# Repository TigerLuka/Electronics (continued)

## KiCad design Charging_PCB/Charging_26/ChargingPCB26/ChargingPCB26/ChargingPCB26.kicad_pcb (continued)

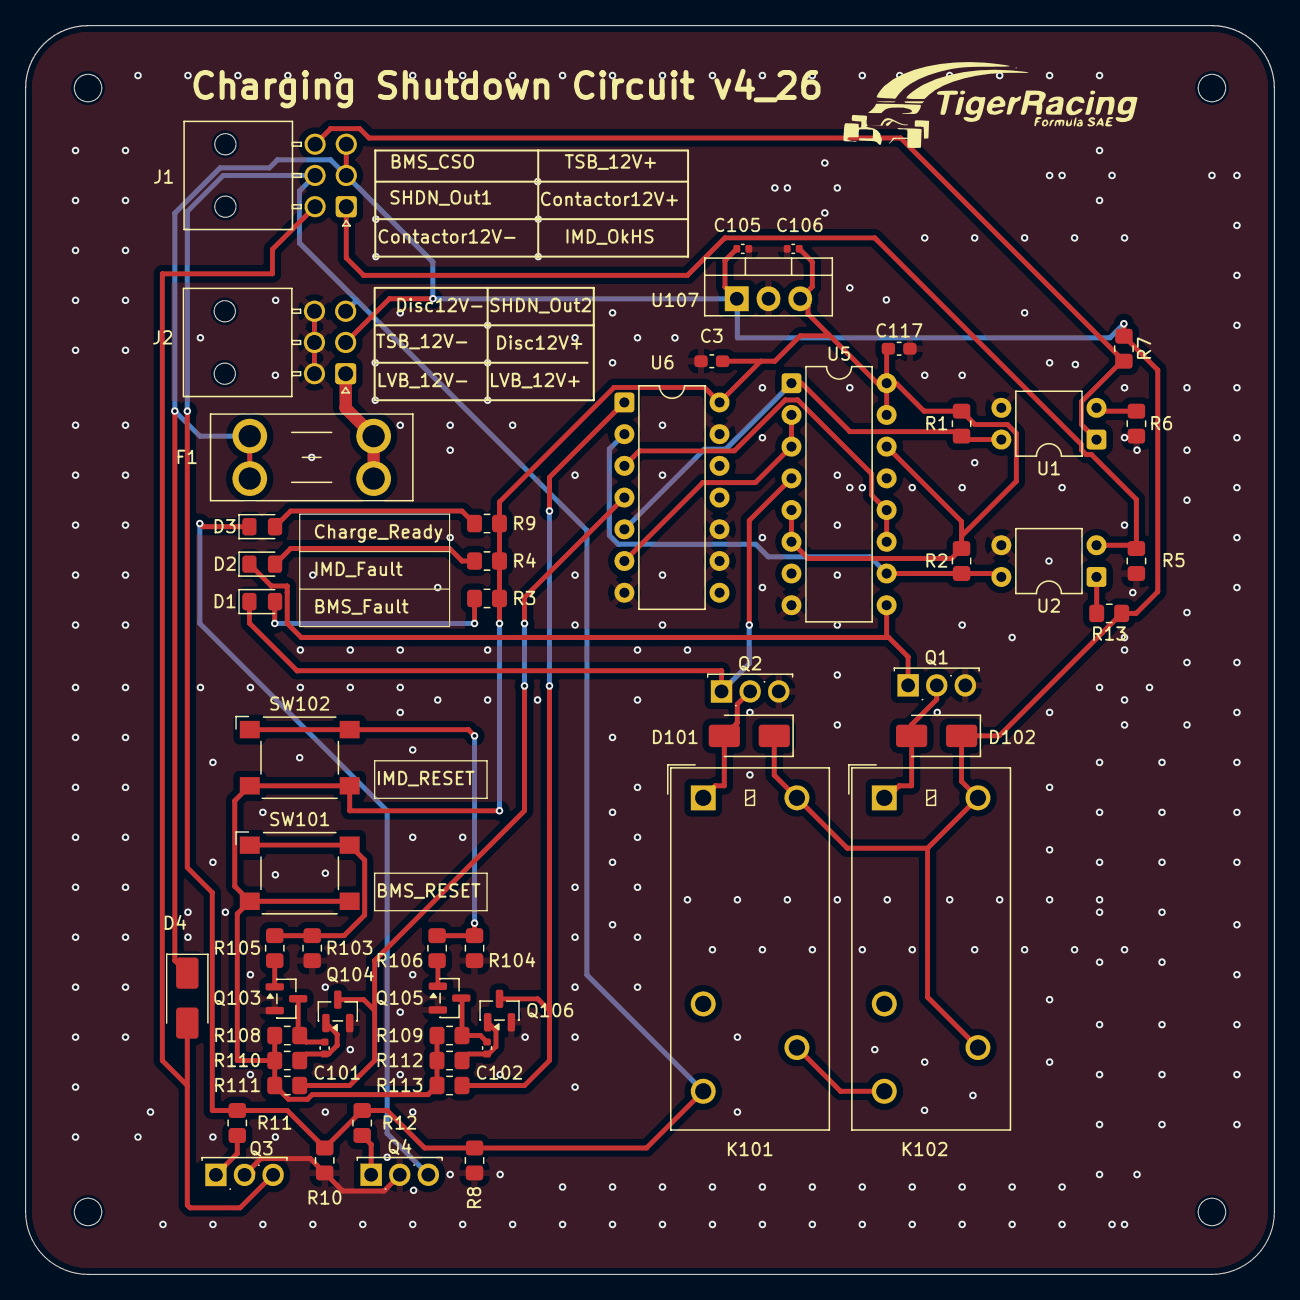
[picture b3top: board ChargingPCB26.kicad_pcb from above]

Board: 2 copper layers, 100.0 x 100.0 mm, 59 parts (0 on the bottom side), 35 nets.

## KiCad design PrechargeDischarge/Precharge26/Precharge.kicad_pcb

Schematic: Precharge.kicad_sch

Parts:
C1, C2, C11, C12, C15, C16, C17, C18, C19, C20, C21, C22, C23: 100n; C_0805_2012Metric_Pad1.15x1.40mm_HandSolder
C3, C8, C9, C10: 1u; C_0805_2012Metric_Pad1.15x1.40mm_HandSolder
C4, C5: 220u; C_Elec_6.3x5.4
C6, C7: 220u; C_Elec_6.3x5.4; not fitted
C13, C14: 10n; C_0805_2012Metric_Pad1.15x1.40mm_HandSolder
D1, D7, D8, D9, D12: D; D_SMA
D2, D3, D4, D5: LED; LED_0805_2012Metric_Castellated
D6: BZX84C3V3; D_SOT-23_ANK
D10, D11: BZX84C12; D_SOT-23_ANK
J1: MicroFit; Molex_Micro-Fit_3.0_43045-0812_2x04_P3.00mm_Vertical
J2: Mini-Fit_Jr_5566-04A; MICROFIT-4PIN
J3: 447690401; MICROFIT-4PIN
JP1, JP2, JP3: SolderJumper_2_Open; SolderJumper-2_P1.3mm_Open_RoundedPad1.0x1.5mm
K1: OMRON-G2RL-24; OMRON-G2R-24; JLC C1524522
K2: G7L-2A-X-L
Q1, Q3: 2N7002; SOT-23
Q2: MMBT3906; SOT-23
R1: 160; R_1206_3216Metric
R2, R3, R4, R5: 200; R_1206_3216Metric
R6, R9: 20k; R_1206_3216Metric
R7, R10, R23, R24: 6k8; R_1206_3216Metric
R8, R21, R27, R29, R44, R45, R48: 10k; R_1206_3216Metric
R11, R12: 1k5; R_1206_3216Metric
R13, R17, R26: 12k; R_1206_3216Metric
R14, R16: 47; R_1206_3216Metric
R15, R18: 560; R_1206_3216Metric
R19, R47: 220; R_1206_3216Metric
R20, R22, R25, R28: 100k; R_1206_3216Metric
R30: 500k; R_1206_3216Metric; not fitted
R31, R32, R33, R34, R36, R37, R38, R40, R41, R42: 510k; R_1206_3216Metric
R35: 2k2; R_1206_3216Metric
R39, R43: 39k; R_1206_3216Metric
R46: HSA253K3J; Chassis_Resistor_TE_Connectivity_HSA25
R49: 0; R_1206_3216Metric
TH1: TFPT1206L1002FM; R_1206_3216Metric
TP1, TP2, TP3, TP4, TP5, TP6: TestPoint; TestPoint_Loop_D2.50mm_Drill1.0mm_LowProfile
U1: TJA1051T-3; SOIC-8_3.9x4.9mm_P1.27mm
U2: SPAN02A-12; DC-DCSPAN02W8-12
U3: Teensy4.0; Teensy40
U4: LM1117-5.0; SOT-223-3_TabPin2
U5, U6, U11: 4N35; SMDIP-6_W7.62mm
U7, U8: LM331; DIP-8_W7.62mm
U9: LM2904; SOIC-8_3.9x4.9mm_P1.27mm
U10: LM393; SOIC-8_3.9x4.9mm_P1.27mm

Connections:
+3V3: R11.2, R12.2, U1.5 (VIO), U3.31
+5V: C8.1, C23.2, D8.2 (A), U1.3 (VCC), U3.33, U4.2 (VO)
+12P: C3.2, C11.1, C12.1, C17.1, C18.1, C22.1, R15.1, R18.2, R23.2, R24.2, R26.1, TH1.2, U2.6 (+Vout), U7.8 (VS), U8.8 (VS), U9.8 (V+), U10.6 (-), U10.8 (V+), U11.1
+12V: C2.1, C4.1, C5.1, C6.1, C7.1, D7.1 (K), D8.1 (K), D9.1 (K), D12.1 (K), K1.8, K2.0, Q2.2 (E), R44.2, U2.2 (+Vin), U4.3 (VI)
/CANH: J1.8, R1.1, U1.7 (CANH)
/CANL: J1.7, R1.2, U1.6 (CANL)
/CANRX: U1.4 (RXD), U3.9
/CANTX: U1.1 (TXD), U3.10
/CFG0: JP1.1 (A), U3.6
/CFG1: JP2.1 (A), U3.7
/CFG2: JP3.1 (A), U3.8
/Faccu: R12.1, TP2.1, U3.21, U6.5
/FoutAccu: TP4.1, U6.2, U8.3 (FOUT)
/FoutTS: TP3.1, U5.2, U7.3 (FOUT)
/Fts: R11.1, TP1.1, U3.22, U5.5
/PDOC_OK: J1.6, Q2.3 (C), R9.1, R45.1
/PRECHG: R47.1, U3.14
/PRECH_STS: J1.4, R8.1
/PWR_OK: C1.1, D6.3 (K), R6.2, R7.1, U3.25
/SHTDN_CTRL: R19.2, U3.13
/SHTDN_OUT: J1.3, K1.4, K1.5, R8.2
/TS-: J3.1, J3.2, R49.1
/VinAccu: K2.2, R31.1, R46.1
/VinTS: J2.4, R33.1, R46.2
GLV+: D1.2 (A), D7.2 (A), J1.1, K1.3, K1.6
GLV-: C1.2, C2.2, C4.2, C5.2, C6.2, C7.2, C8.2, C23.1, D6.1 (A), J1.5, JP1.2 (B), JP2.2 (B), JP3.2 (B), Q1.2 (S), Q3.2 (S), R2.2, R3.2, R4.2, R5.2, R7.2, R10.2, R21.2, R45.2, R48.2, U1.2 (GND), U1.8 (S), U2.1 (-Vin), U3.1, U3.17, U3.32, U4.1 (GND), U5.4, U6.4, U11.4
GNDS: C3.1, C11.2, C12.2, C13.2, C14.2, C15.2, C16.2, C18.2, C19.2, C20.2, C21.2, C22.2, D10.1 (A), D11.1 (A), R13.1, R14.1, R16.1, R17.1, R27.2, R29.2, R39.2, R43.2, R49.2, U2.7 (-Vout), U7.4 (GND), U8.4 (GND), U9.4 (V-), U10.4 (V-), U10.5 (+)
unnamed: C9.2, R14.2, R20.2
unnamed: C10.2, R16.2, R22.2
unnamed: D1.1 (K), R6.1
unnamed: D2.1 (K), R2.1
unnamed: D3.1 (K), R3.1
unnamed: D4.1 (K), R4.1
unnamed: D5.1 (K), R5.1
unnamed: D9.2 (A), K1.1, Q1.3 (D)
unnamed: C20.1, D10.3 (K), R38.2, R39.1, TP5.1, U9.3 (+)
unnamed: C21.1, D11.3 (K), R42.2, R43.1, TP6.1, U9.5 (+)
unnamed: D12.2 (A), K2.1, Q3.3 (D)
unnamed: J2.1, K2.8
unnamed: K2.4, K2.6
unnamed: Q1.1 (G), R19.1, R21.1
unnamed: Q2.1 (B), R44.1, U11.5
unnamed: Q3.1 (G), R47.2, R48.1
unnamed: R9.2, R10.1, U3.28
unnamed: R15.2, U5.1
unnamed: R18.1, U6.1
unnamed: R30.1, R35.2, U10.1
unnamed: R31.2, R32.1
unnamed: R32.2, R36.1
unnamed: R33.2, R34.1
unnamed: R34.2, R40.1
unnamed: R35.1, U11.2
unnamed: R36.2, R37.1
unnamed: R37.2, R38.1
unnamed: R40.2, R41.1
unnamed: R41.2, R42.1
unnamed: C15.1, R25.2, U7.7 (CIN)
unnamed: C9.1, R20.1, U7.1 (IOUT), U7.6 (THR)
unnamed: R13.2, U7.2 (IREF)
unnamed: C13.1, R23.1, U7.5 (RC)
unnamed: C16.1, R28.2, U8.7 (CIN)
unnamed: C10.1, R22.1, U8.1 (IOUT), U8.6 (THR)
unnamed: R17.2, U8.2 (IREF)
unnamed: C14.1, R24.1, U8.5 (RC)
unnamed: R28.1, U9.1, U9.2 (-)
unnamed: R25.1, U9.6 (-), U9.7
unnamed: C19.1, R26.2, R27.1, R30.2, U10.3 (+)
unnamed: C17.2, R29.1, TH1.1, U10.2 (-)

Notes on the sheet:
ToDo: Replace relay
Resistors: Use 1% or better
C6, C7 not populated
Separate ground-in net protects current path
Shutdown Circuit IN
PDOC - Thermal overload protection for precharge resistor
Not populated
PRECHARGE

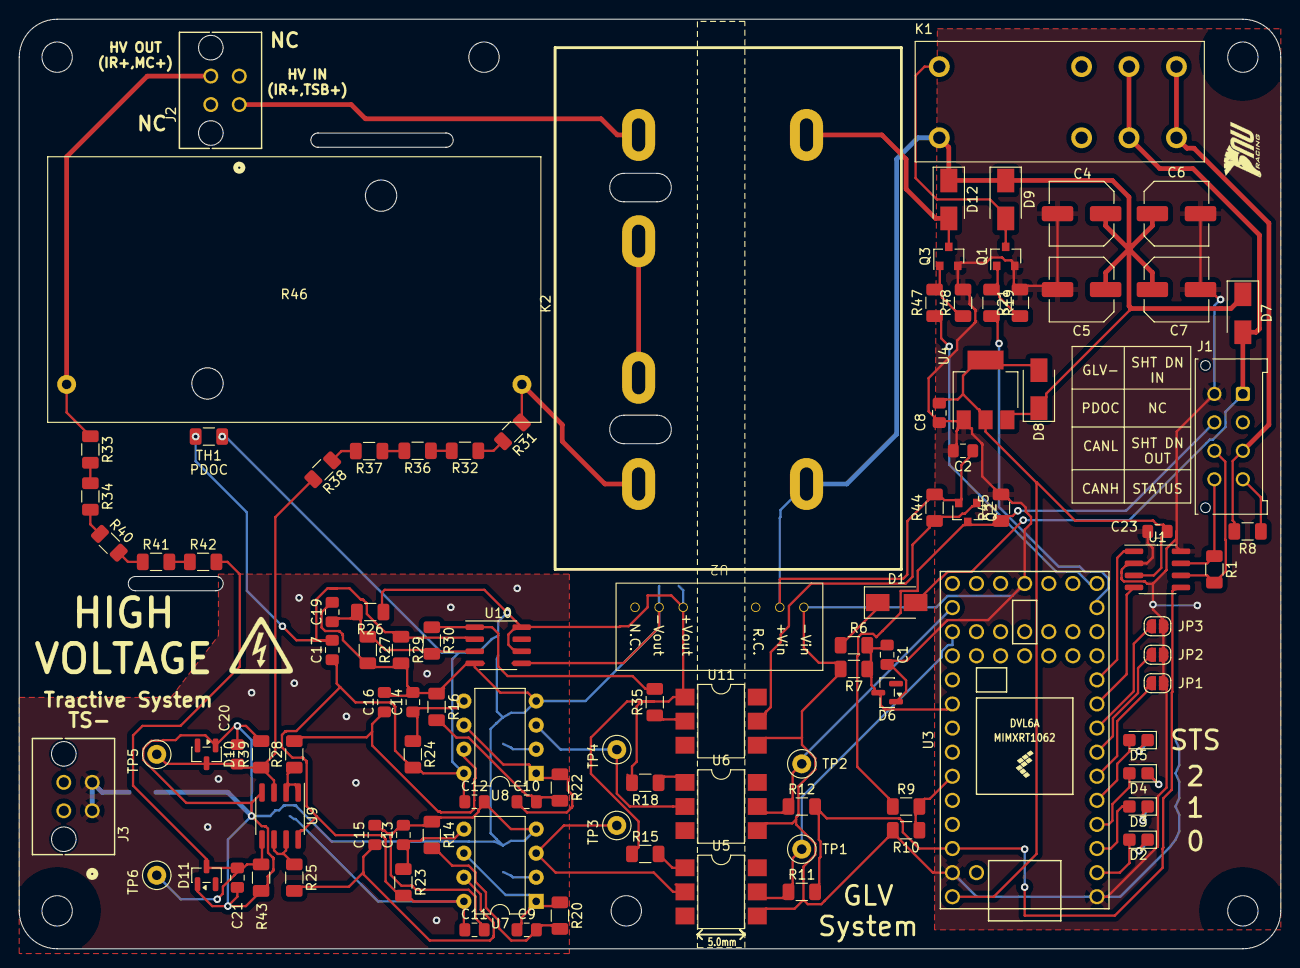
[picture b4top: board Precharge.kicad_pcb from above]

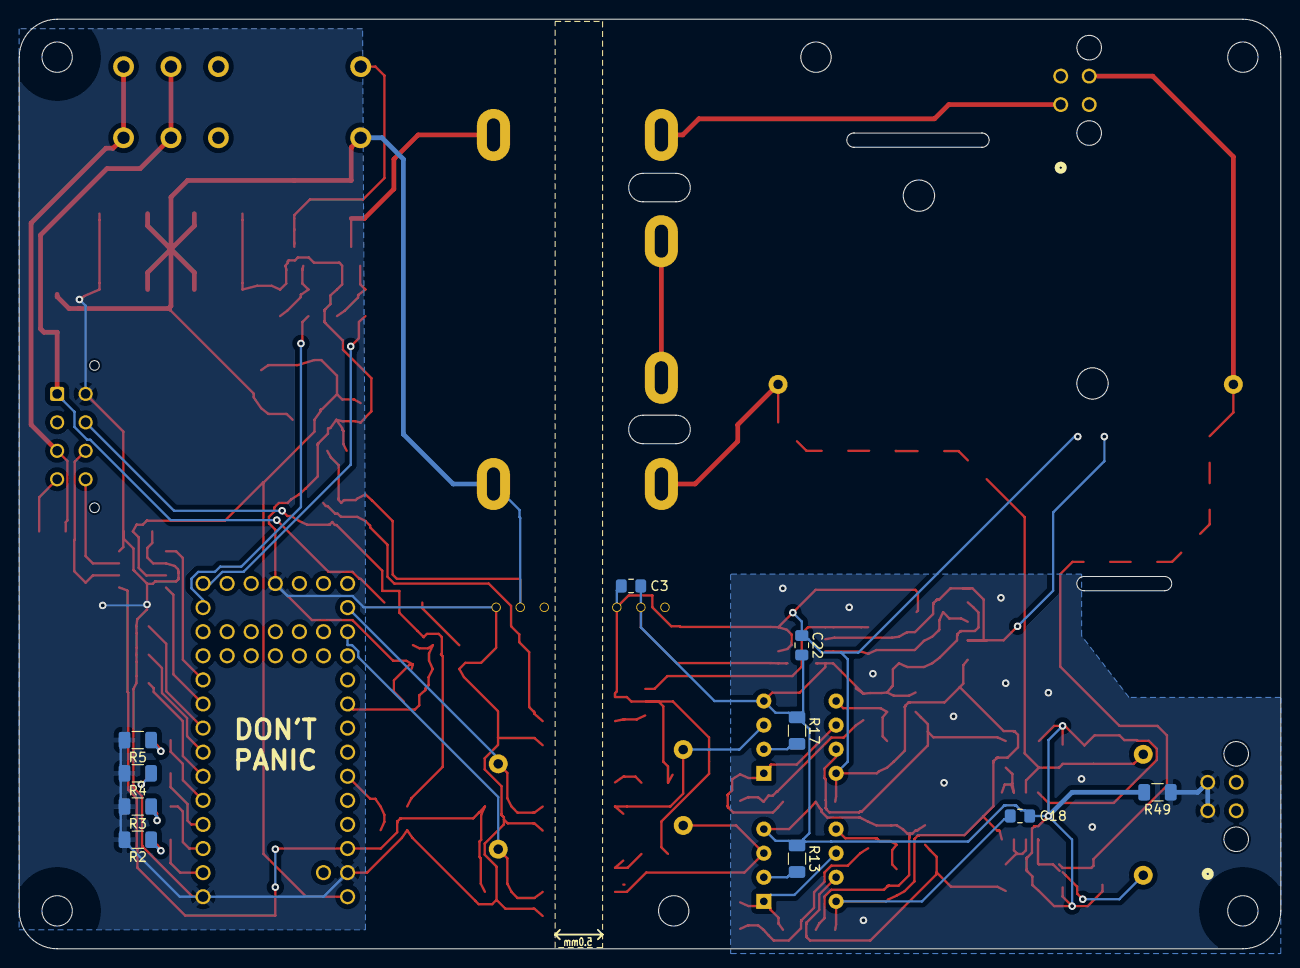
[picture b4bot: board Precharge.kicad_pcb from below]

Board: 2 copper layers, 133.0 x 98.0 mm, 119 parts (10 on the bottom side), 68 nets.

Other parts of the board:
MT1, MT2, MT3, MT4, MT5, MT6: MountingHole_3.2mm_M3

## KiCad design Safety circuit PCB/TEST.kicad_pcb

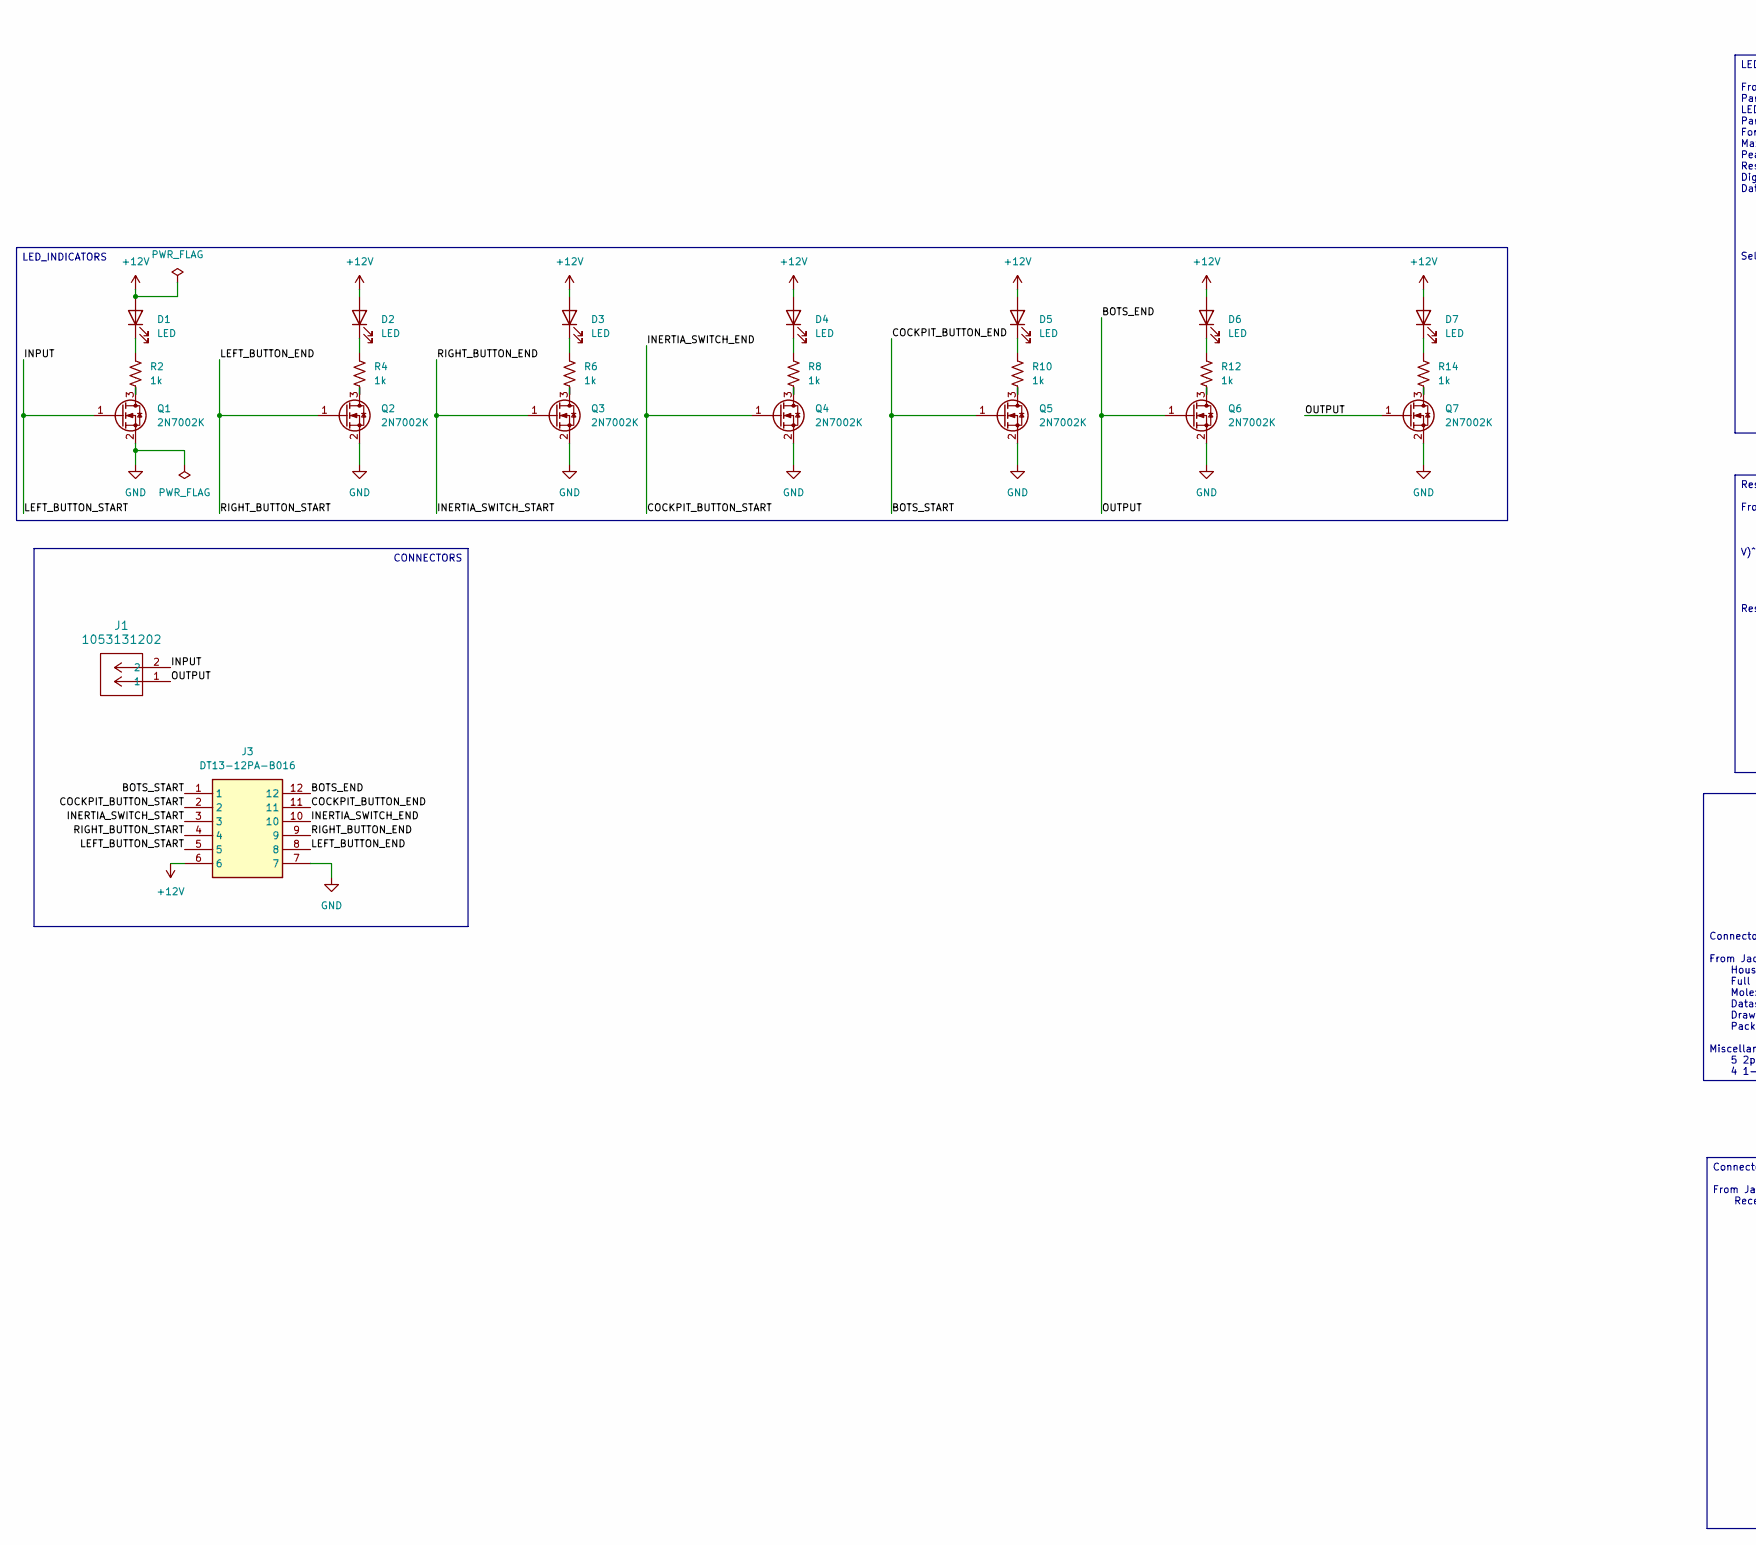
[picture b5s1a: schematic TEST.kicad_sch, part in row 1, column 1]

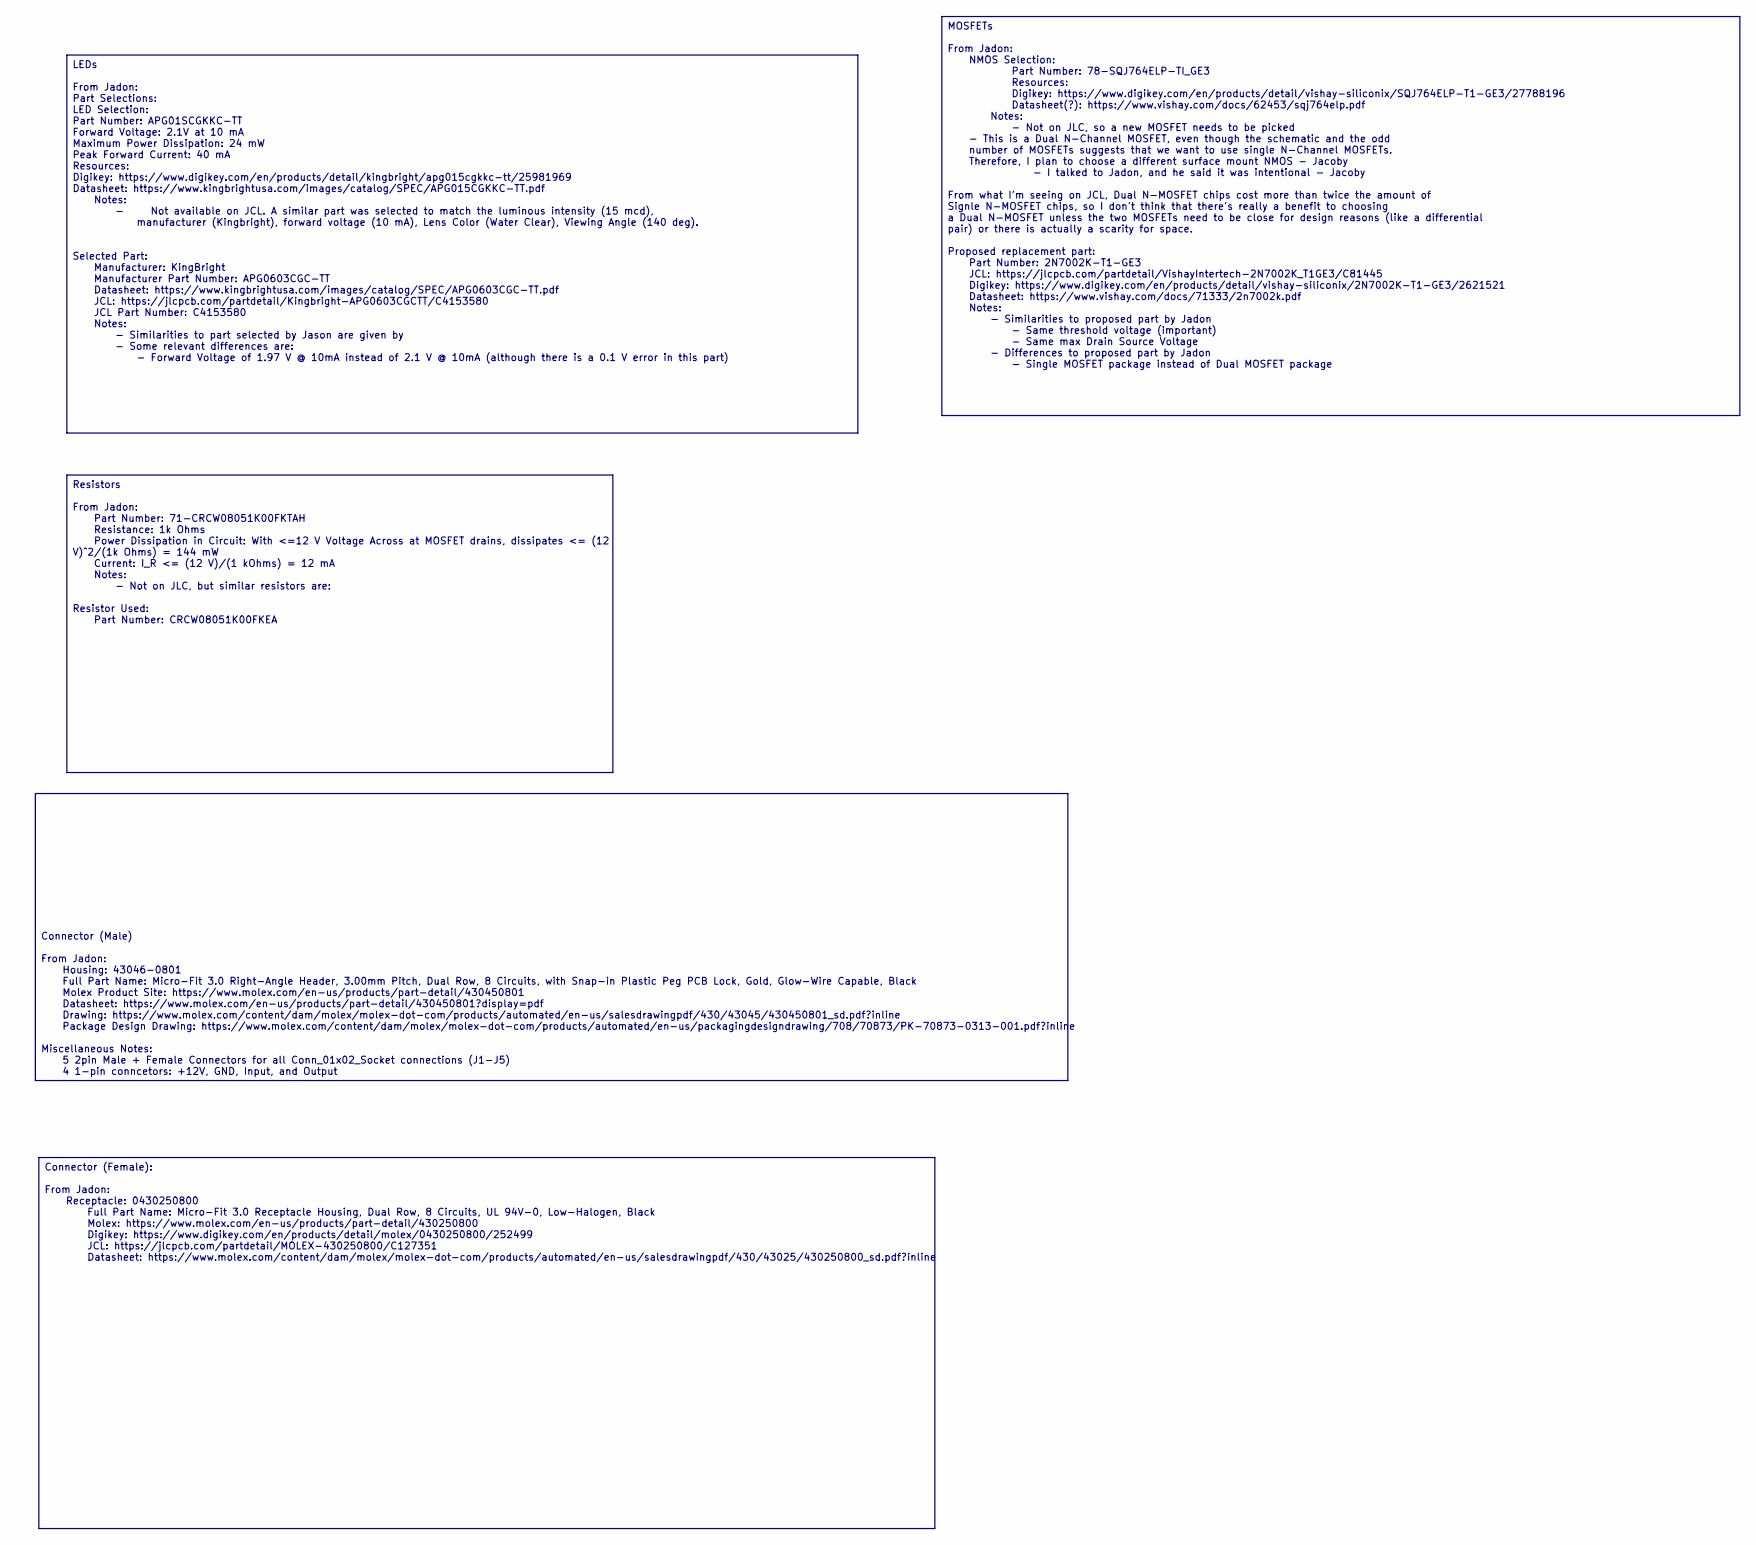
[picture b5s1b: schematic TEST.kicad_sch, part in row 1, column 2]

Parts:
D1, D2, D3, D4, D5, D6, D7: LED; HL-PSC-1608U52GC-G4; MFR Part # PSC-1608U50GC-G4; JLC Part # C22371297
J1: 1053131202; CONN_SD-105313-100_02_MOL; MFR Part # 1053131202; JLC Part # C586242
J3: DT13-12PA-B016; DT1312PAB016; MFR Part # DT13-12PA-B016; JLC Part # C17266705
Q1, Q2, Q3, Q4, Q5, Q6, Q7: 2N7002K; SOT-23; MFR Part # 2N7002K-T1-GE3; JLC Part # C81445
R2, R4, R6, R8, R10, R12, R14: 1k; CRCW0805; MFR Part # CRCW08051K00FKEA; JLC Part # C844939

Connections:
+12V: D1.2 (A), D2.2 (A), D3.2 (A), D4.2 (A), D5.2 (A), D6.2 (A), D7.2 (A), J3.6
/BOTS_END: J1.1, J3.12, Q6.1 (G), Q7.1 (G)
/BOTS_START: J3.1, J3.11, Q5.1 (G)
/COCKPIT_BUTTON_START: J3.2, J3.10, Q4.1 (G)
/INERTIA_SWITCH_START: J3.3, J3.9, Q3.1 (G)
/INPUT: J1.2, J3.5, Q1.1 (G)
/LEFT_BUTTON_END: J3.4, J3.8, Q2.1 (G)
GND: J3.7, Q1.2 (S), Q2.2 (S), Q3.2 (S), Q4.2 (S), Q5.2 (S), Q6.2 (S), Q7.2 (S)
unnamed: D1.1 (K), R2.1
unnamed: D2.1 (K), R4.1
unnamed: D3.1 (K), R6.1
unnamed: D4.1 (K), R8.1
unnamed: D5.1 (K), R10.1
unnamed: D6.1 (K), R12.1
unnamed: D7.1 (K), R14.1
unnamed: Q1.3 (D), R2.2
unnamed: Q2.3 (D), R4.2
unnamed: Q3.3 (D), R6.2
unnamed: Q4.3 (D), R8.2
unnamed: Q5.3 (D), R10.2
unnamed: Q6.3 (D), R12.2
unnamed: Q7.3 (D), R14.2

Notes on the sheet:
LEDs From Jadon: Part Selections: LED Selection: Part Number: APG01SCGKKC-TT Forward Voltage: 2.1V at 10 mA Maximum Power Dissipation: 24 mW Peak Forward Current: 40 mA Resources: Digikey: https://www.digikey.com/en/products/detail/kingbright/apg015cgkkc-tt/25981969 Datasheet: https://www.kingbrigh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
CONNECTORS
Connector (Male) From Jadon: Housing: 43046-0801 Full Part Name: Micro-Fit 3.0 Right-Angle Header, 3.00mm Pitch, Dual Row, 8 Circuits, with Snap-in Plastic Peg PCB Lock, Gold, Glow-Wire Capable, Black Molex Product Site: https://www.molex.com/en-us/products/part-detail/430450801 Datasheet: https://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
Connector (Female): From Jadon: Receptacle: 0430250800 Full Part Name: Micro-Fit 3.0 Receptacle Housing, Dual Row, 8 Circuits, UL 94V-0, Low-Halogen, Black Molex: https://www.molex.com/en-us/products/part-detail/430250800 Digikey: https://www.digikey.com/en/products/detail/molex/0430250800/252499 J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
LED_INDICATORS
Resistors From Jadon: Part Number: 71-CRCW08051K00FKTAH Resistance: 1k Ohms Power Dissipation in Circuit: With <=12 V Voltage Across at MOSFET drains, dissipates <= (12 V)^2/(1k Ohms) = 144 mW Current: I_R <= (12 V)/(1 kOhms) = 12 mA Notes: - Not on JLC, but similar resistors are: Resistor Used: Pa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
MOSFETs From Jadon: NMOS Selection: Part Number: 78-SQJ764ELP-TI_GE3 Resources: Digikey: https://www.digikey.com/en/products/detail/vishay-siliconix/SQJ764ELP-T1-GE3/27788196 Datasheet(?): https://www.vishay.com/docs/62453/sqj764elp.pdf Notes: - Not on JLC, so a new MOSFET needs to be picked - This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

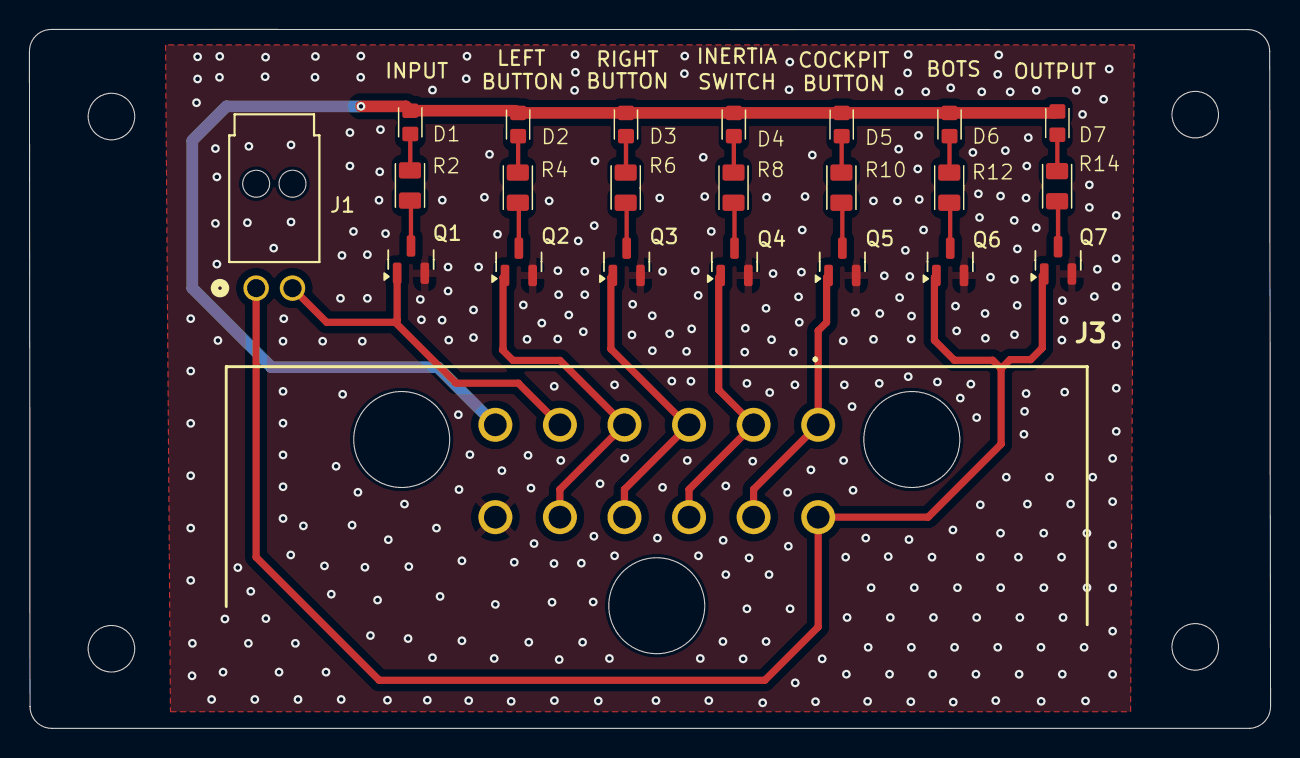
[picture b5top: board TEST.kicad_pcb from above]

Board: 2 copper layers, 85.3 x 48.1 mm, 23 parts (0 on the bottom side), 22 nets.
